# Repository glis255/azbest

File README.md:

# Azbest-3
Sterownik dzwonków szkolnych

## Zawartość
- [Firmware](firmware/) → Oprogramowanie
- [Hardware 3D print](hardware-3d-print/) → Obudowa do druku 3D *(będzie kiedyś)*
- [Hardware PCB](hardware-pcb/) → Schemat oraz płytka drukowana

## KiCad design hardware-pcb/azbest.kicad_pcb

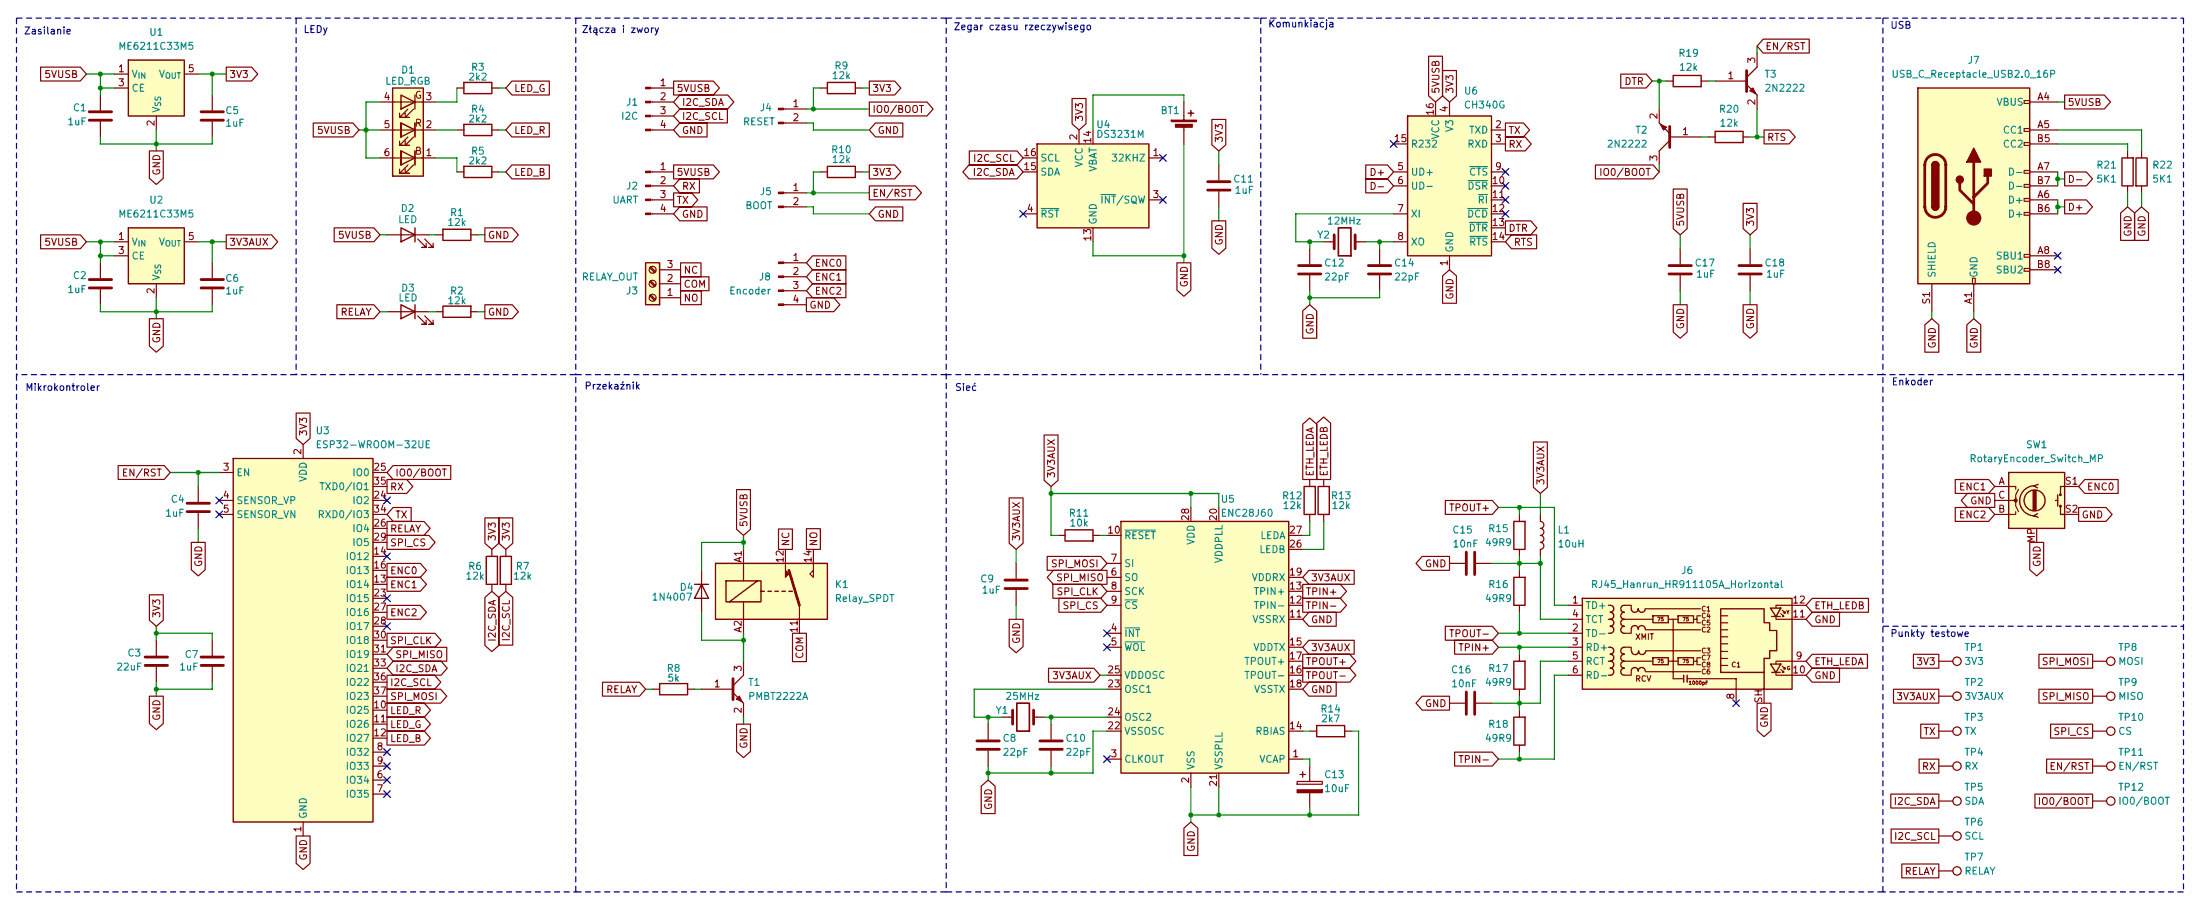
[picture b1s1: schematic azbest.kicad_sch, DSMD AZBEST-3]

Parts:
BT1: Battery_Cell; Battery_Panasonic_CR2032-HFN_Horizontal_CircularHoles
C1, C2, C4, C5, C6, C7, C9, C11, C17, C18: 1uF; C_0603_1608Metric_Pad1.08x0.95mm_HandSolder
C3: 22uF; C_0603_1608Metric_Pad1.08x0.95mm_HandSolder
C8, C10: 22pF; C_0805_2012Metric_Pad1.18x1.45mm_HandSolder
C12, C14: 22pF; C_0603_1608Metric_Pad1.08x0.95mm_HandSolder
C13: 10uF; CP_EIA-6032-28_Kemet-C_Pad2.25x2.35mm_HandSolder
C15, C16: 10nF; C_0805_2012Metric_Pad1.18x1.45mm_HandSolder
D1: LED_RGB; LED_RGB_5050-6
D2, D3: LED; LED_0805_2012Metric_Pad1.15x1.40mm_HandSolder
D4: 1N4007; D_DO-41_SOD81_P10.16mm_Horizontal
J1: I2C; JST_XH_B4B-XH-A_1x04_P2.50mm_Vertical
J2: UART; PinHeader_1x04_P2.54mm_Vertical
J3: RELAY_OUT; TerminalBlock_Phoenix_MKDS-1,5-3_1x03_P5.00mm_Horizontal
J4: RESET; PinHeader_1x02_P2.54mm_Vertical
J5: BOOT; PinHeader_1x02_P2.54mm_Vertical
J6: RJ45_Hanrun_HR911105A_Horizontal
J7: USB_C_Receptacle_USB2.0_16P; USB_C_Receptacle_GCT_USB4105-xx-A_16P_TopMnt_Horizontal
J8: Encoder; JST_XH_B4B-XH-A_1x04_P2.50mm_Vertical
K1: Relay_SPDT; Relay_SPDT_Hongfa_HF3F-L-xx-1ZL1T
L1: 10uH; L_0805_2012Metric_Pad1.15x1.40mm_HandSolder
R1, R2, R6, R7, R9, R10, R19, R20: 12k; R_0603_1608Metric_Pad0.98x0.95mm_HandSolder
R3, R4, R5: 2k2; R_0603_1608Metric_Pad0.98x0.95mm_HandSolder
R8: 5k; R_0603_1608Metric_Pad0.98x0.95mm_HandSolder
R11: 10k; R_0805_2012Metric_Pad1.20x1.40mm_HandSolder
R12, R13: 12k; R_0805_2012Metric_Pad1.20x1.40mm_HandSolder
R14: 2k7; R_0805_2012Metric_Pad1.20x1.40mm_HandSolder
R15, R16, R17, R18: 49R9; R_0805_2012Metric_Pad1.20x1.40mm_HandSolder
R21, R22: 5K1; R_0603_1608Metric_Pad0.98x0.95mm_HandSolder
SW1: RotaryEncoder_Switch_MP; RotaryEncoder_Alps_EC12E-Switch_Vertical_H20mm
T1: PMBT2222A; SOT-23_Handsoldering
T2, T3: 2N2222; SOT-23_Handsoldering
TP1: 3V3; TestPoint_Pad_D1.0mm
TP2: 3V3AUX; TestPoint_Pad_D1.0mm
TP3: TX; TestPoint_Pad_D1.0mm
TP4: RX; TestPoint_Pad_D1.0mm
TP5: SDA; TestPoint_Pad_D1.0mm
TP6: SCL; TestPoint_Pad_D1.0mm
TP7: RELAY; TestPoint_Pad_D1.0mm
TP8: MOSI; TestPoint_Pad_D1.0mm
TP9: MISO; TestPoint_Pad_D1.0mm
TP10: CS; TestPoint_Pad_D1.0mm
TP11: EN/RST; TestPoint_Pad_D1.0mm
TP12: IO0/BOOT; TestPoint_Pad_D1.0mm
U1, U2: ME6211C33M5; SOT-23-5
U3: ESP32-WROOM-32UE
U4: DS3231M; SOIC-16W_7.5x10.3mm_P1.27mm
U5: ENC28J60; SOIC-28W_7.5x17.9mm_P1.27mm
U6: CH340G; SOIC-16_3.9x9.9mm_P1.27mm
Y1: 25MHz; Crystal_HC49-U_Vertical
Y2: 12MHz; Crystal_SMD_HC49-SD

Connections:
3V3: C3.1, C5.1, C7.1, C11.1, C18.1, R6.2, R7.1, R9.2, R10.2, TP1.1, U1.5 (V_{OUT}), U3.2 (VDD), U4.2 (VCC), U6.4 (V3)
3V3AUX: C6.1, C9.1, L1.1, R11.1, TP2.1, U2.5 (V_{OUT}), U5.15 (VDDTX), U5.19 (VDDRX), U5.20 (VDDPLL), U5.25 (VDDOSC), U5.28 (VDD)
5VUSB: C1.1, C2.1, C17.1, D1.4 (BA), D1.5 (GA), D1.6 (RA), D2.2 (A), D4.1 (K), J1.1, J2.1, J7.A4 (VBUS), J7.A9 (VBUS), J7.B4 (VBUS), J7.B9 (VBUS), K1.A1, U1.1 (V_{IN}), U1.3 (CE), U2.1 (V_{IN}), U2.3 (CE), U6.16 (VCC)
COM: J3.2, K1.11
D+: J7.A6 (D+), J7.B6 (D+), U6.5 (UD+)
D-: J7.A7 (D-), J7.B7 (D-), U6.6 (UD-)
DTR: R19.1, T2.2 (E), U6.13 (~DTR)
ENC0: J8.1, SW1.S1, U3.16 (IO13)
ENC1: J8.2, SW1.A, U3.13 (IO14)
ENC2: J8.3, SW1.B, U3.27 (IO16)
EN/RST: C4.1, J5.1, R10.1, T3.3 (C), TP11.1, U3.3 (EN)
ETH_LEDA: J6.9, R12.2
ETH_LEDB: J6.12, R13.2
GND: BT1.2 (-), C1.2, C2.2, C3.2, C4.2, C5.2, C6.2, C7.2, C8.2, C9.2, C10.2, C11.2, C12.2, C13.2, C14.2, C15.1, C16.1, C17.2, C18.2, J1.4, J2.4, J4.2, J5.2, J6.10, J6.11, J6.SH, J7.A1 (GND), J7.A12 (GND), J7.B1 (GND), J7.B12 (GND), J7.S1 (SHIELD), J8.4, R1.1, R2.2, R14.2, R21.1, R22.2, SW1.C, SW1.MP, SW1.S2, T1.2 (E), U1.2 (V_{SS}), U2.2 (V_{SS}), U3.1 (GND), U3.15 (GND), U3.38 (GND), U3.39 (GND), U4.5 (GND), U4.6 (GND), U4.7 (GND), U4.8 (GND), U4.9 (GND), U4.10 (GND), U4.11 (GND), U4.12 (GND), U4.13 (GND), U5.2 (VSS), U5.11 (VSSRX), U5.18 (VSSTX), U5.21 (VSSPLL), U5.22 (VSSOSC), U6.1 (GND)
I2C_SCL: J1.3, R7.2, TP6.1, U3.36 (IO22), U4.16 (SCL)
I2C_SDA: J1.2, R6.1, TP5.1, U3.33 (IO21), U4.15 (SDA)
IO0/BOOT: J4.1, R9.1, T2.3 (C), TP12.1, U3.25 (IO0)
LED_B: R5.1, U3.12 (IO27)
LED_G: R3.1, U3.11 (IO26)
LED_R: R4.1, U3.10 (IO25)
NC: J3.3, K1.12
NO: J3.1, K1.14
unnamed: BT1.1 (+), U4.14 (VBAT)
unnamed: D1.3 (BK), R3.2
unnamed: D1.2 (GK), R4.2
unnamed: D1.1 (RK), R5.2
unnamed: D2.1 (K), R1.2
unnamed: D3.1 (K), R2.1
unnamed: D4.2 (A), K1.A2, T1.3 (C)
unnamed: C16.2, J6.5 (RCT), R17.1, R18.2
unnamed: C15.2, J6.4 (TCT), L1.2, R15.1, R16.2
unnamed: J7.A5 (CC1), R22.1
unnamed: J7.B5 (CC2), R21.2
unnamed: R8.2, T1.1 (B)
unnamed: R20.1, T2.1 (B)
unnamed: R19.2, T3.1 (B)
unnamed: R12.1, U5.27 (LEDA)
unnamed: R13.1, U5.26 (LEDB)
unnamed: C8.1, U5.23 (OSC1), Y1.2
unnamed: C10.1, U5.24 (OSC2), Y1.1
unnamed: R14.1, U5.14 (RBIAS)
unnamed: C13.1, U5.1 (VCAP)
unnamed: R11.2, U5.10 (~RESET)
unnamed: C12.1, U6.7 (XI), Y2.2
unnamed: C14.1, U6.8 (XO), Y2.1
RELAY: D3.2 (A), R8.1, TP7.1, U3.26 (IO4)
RTS: R20.2, T3.2 (E), U6.14 (~RTS)
RX: J2.2, TP4.1, U3.35 (TXD0/IO1), U6.3 (RXD)
SPI_CLK: U3.30 (IO18), U5.8 (SCK)
SPI_CS: TP10.1, U3.29 (IO5), U5.9 (~CS)
SPI_MISO: TP9.1, U3.31 (IO19), U5.6 (SO)
SPI_MOSI: TP8.1, U3.37 (IO23), U5.7 (SI)
TPIN+: J6.3 (RD+), R17.2, U5.13 (TPIN+)
TPIN-: J6.6 (RD-), R18.1, U5.12 (TPIN-)
TPOUT+: J6.1 (TD+), R15.2, U5.17 (TPOUT+)
TPOUT-: J6.2 (TD-), R16.1, U5.16 (TPOUT-)
TX: J2.3, TP3.1, U3.34 (RXD0/IO3), U6.2 (TXD)

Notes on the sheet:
LEDy
Punkty testowe
Przekaźnik
Enkoder
Złącza i zwory
Sieć
Zasilanie
Komunkiacja
Zegar czasu rzeczywisego
Mikrokontroler
USB

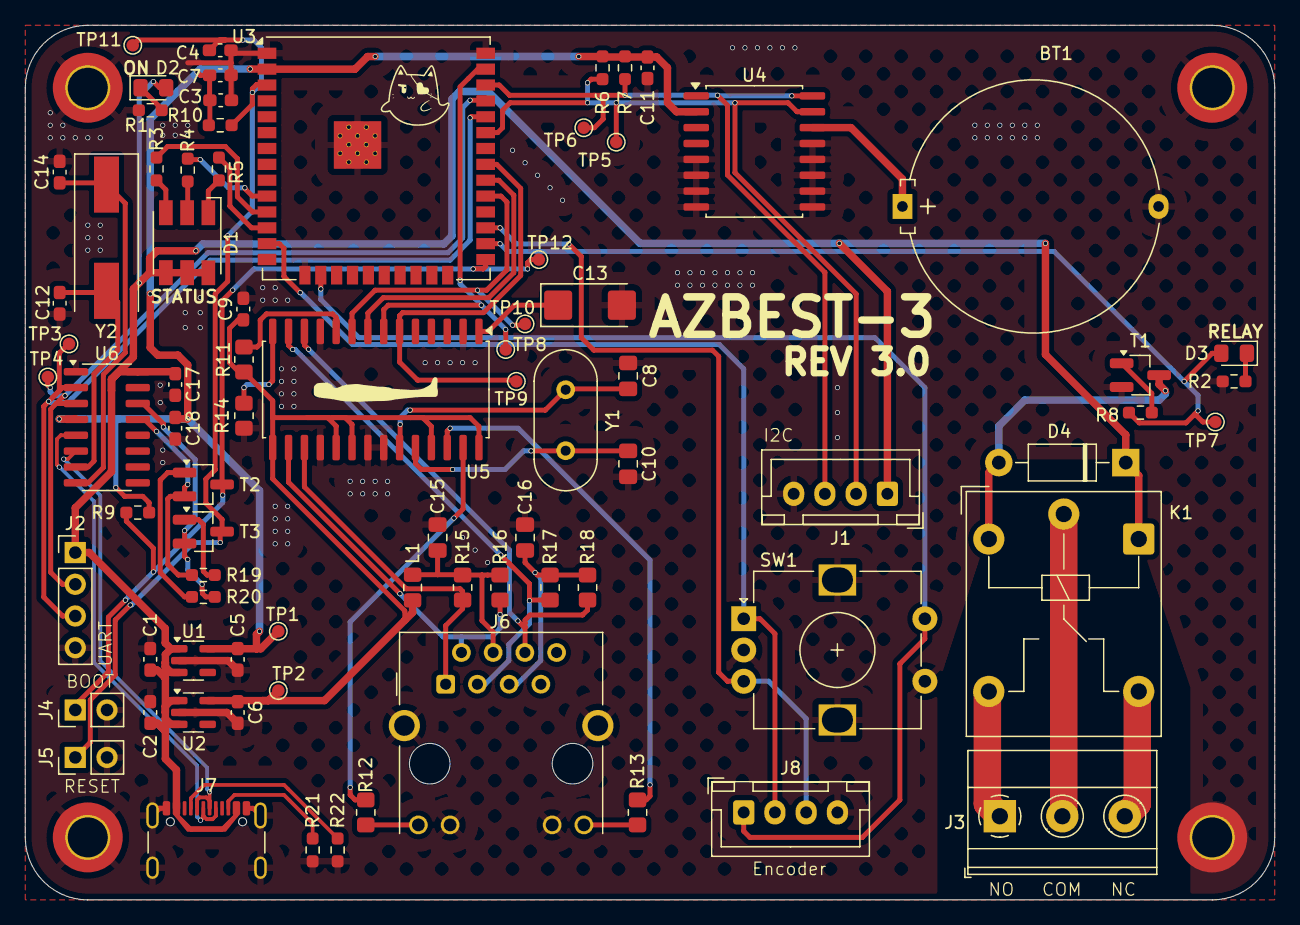
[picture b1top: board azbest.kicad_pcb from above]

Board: 2 copper layers, 100.0 x 70.0 mm, 79 parts (0 on the bottom side), 57 nets.

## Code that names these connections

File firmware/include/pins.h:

#if SERIAL_NUMBER == 1
    #define RELAY_PIN 17
    #define LED_R_PIN 25
    #define LED_G_PIN 27
    #define LED_B_PIN 26
    #define ENC_BTN_PIN 13
    #define ENC_A_PIN 16
    #define ENC_B_PIN 14
#else
    #define RELAY_PIN 4
    #define LED_R_PIN 25
    #define LED_G_PIN 27
    #define LED_B_PIN 26
    #define ENC_BTN_PIN 13
    #define ENC_A_PIN 14
    #define ENC_B_PIN 16
#endif
